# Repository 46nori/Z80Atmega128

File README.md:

# Z80ATmega128

[日本語版READMEはこちら](./README-ja.md)

## Overview

This project aims to build a Z80A system and run CP/M-80 natively on it.

You might be wondering why I chose the Z80 today. Well, it happened to be discovered in my collection of electronic components after being tucked away for 30 years. Moreover, it's an original Zilog Z80A from the NMOS process era, likely manufactured around 1980!  

However, rather than simply replicating a single-board microcontroller system from the 1980s, I've decided to take a different approach. Reproducing such a system lacks novelty and excitement, not to mention the difficulty of sourcing the necessary parts.

Hence, I've devised the following design principles:

1. A hybrid configuration utilizing both [Z80A](https://www.zilog.com/docs/z80/um0080.pdf) and [ATmega128-16AU](https://www.microchip.com/en-us/product/ATmega128) (AVR) microcontrollers.
2. I won't be using ROM; instead, a 64KB SRAM will be shared between the Z80A and AVR. AVR will manage the placement of the Z80's bootstrap code.
3. AVR firmware will handle the Z80 hardware I/O and interrupt cycles completely. **Any Z80's I/O devices can, in principle, be described by software!**
4. Design circuits using components that are as easy to procure as possible. (As of 2023, mainly in the Japanese electronic parts market.)

## Achievements

* CP/M 2.2 works directly on the Z80 processor.
* The system can boot CP/M from a microSD card containing the CP/M image file.
* CP/M 3 (Non-banked memory version) works as well.
* You can enjoy playing the text adventure game ZORK I, II and III !
* The printed circuit board (PCB) is available.
* Demo Video  

## Contents

```text
.
├── avr                      AVR firmware
├── z80                      Z80 software
│   ├── cpm22                CP/M-80 Ver2.2
│   │   ├── bios               BIOS
│   │   ├── sys                CPM.SYS(CCP/BDOS) and cpm.ihx(IPL+CCP/BDOS+BIOS)
│   │   └── image              CP/M 2.2 Disk image
│   └── cpm3                 CP/M 3 (CP/M Plus)
│       └── image              CP/M 3 Disk image
├── doc
│   ├── Hardware/            Hardware documents
│   ├── Software/            Software documents
│   └── README.md            Table of contents
└── schematics
    └── KiCad
        ├── *.kicad_sch      Schematic diagram
        └── *.kicad_pcb      PCB diagram
```

* [Document](doc/README.md)
  * [Z80ATmega128 Board Setup Guide](doc/SetupGuide_en.md)
  * [Hardware design document](doc/Hardware/Design.md)
* [Development log](doc/Diary.md)

## Required tools

* [Microchip Studio](https://www.microchip.com/en-us/tools-resources/develop/microchip-studio) for AVR v7.0 or later is required to build avr/.
* [AVRISP mkII](https://www.microchip.com/en-us/development-tool/ATAVRISP2) is required to program software(avr/) into ATmega128.
* Schematics and PCB are designed by [KiCad](https://www.kicad.org/) v7.0.
* [ASxxxx Cross Assemblers](https://shop-pdp.net/ashtml/asxxxx.php) to build the CP/M BIOS in z80/.
* [cpmtools](https://github.com/lipro-cpm4l/cpmtools) for creating CP/M disk images.

## Prototype

## PCB

## Schematic diagram

## License

GPLv3

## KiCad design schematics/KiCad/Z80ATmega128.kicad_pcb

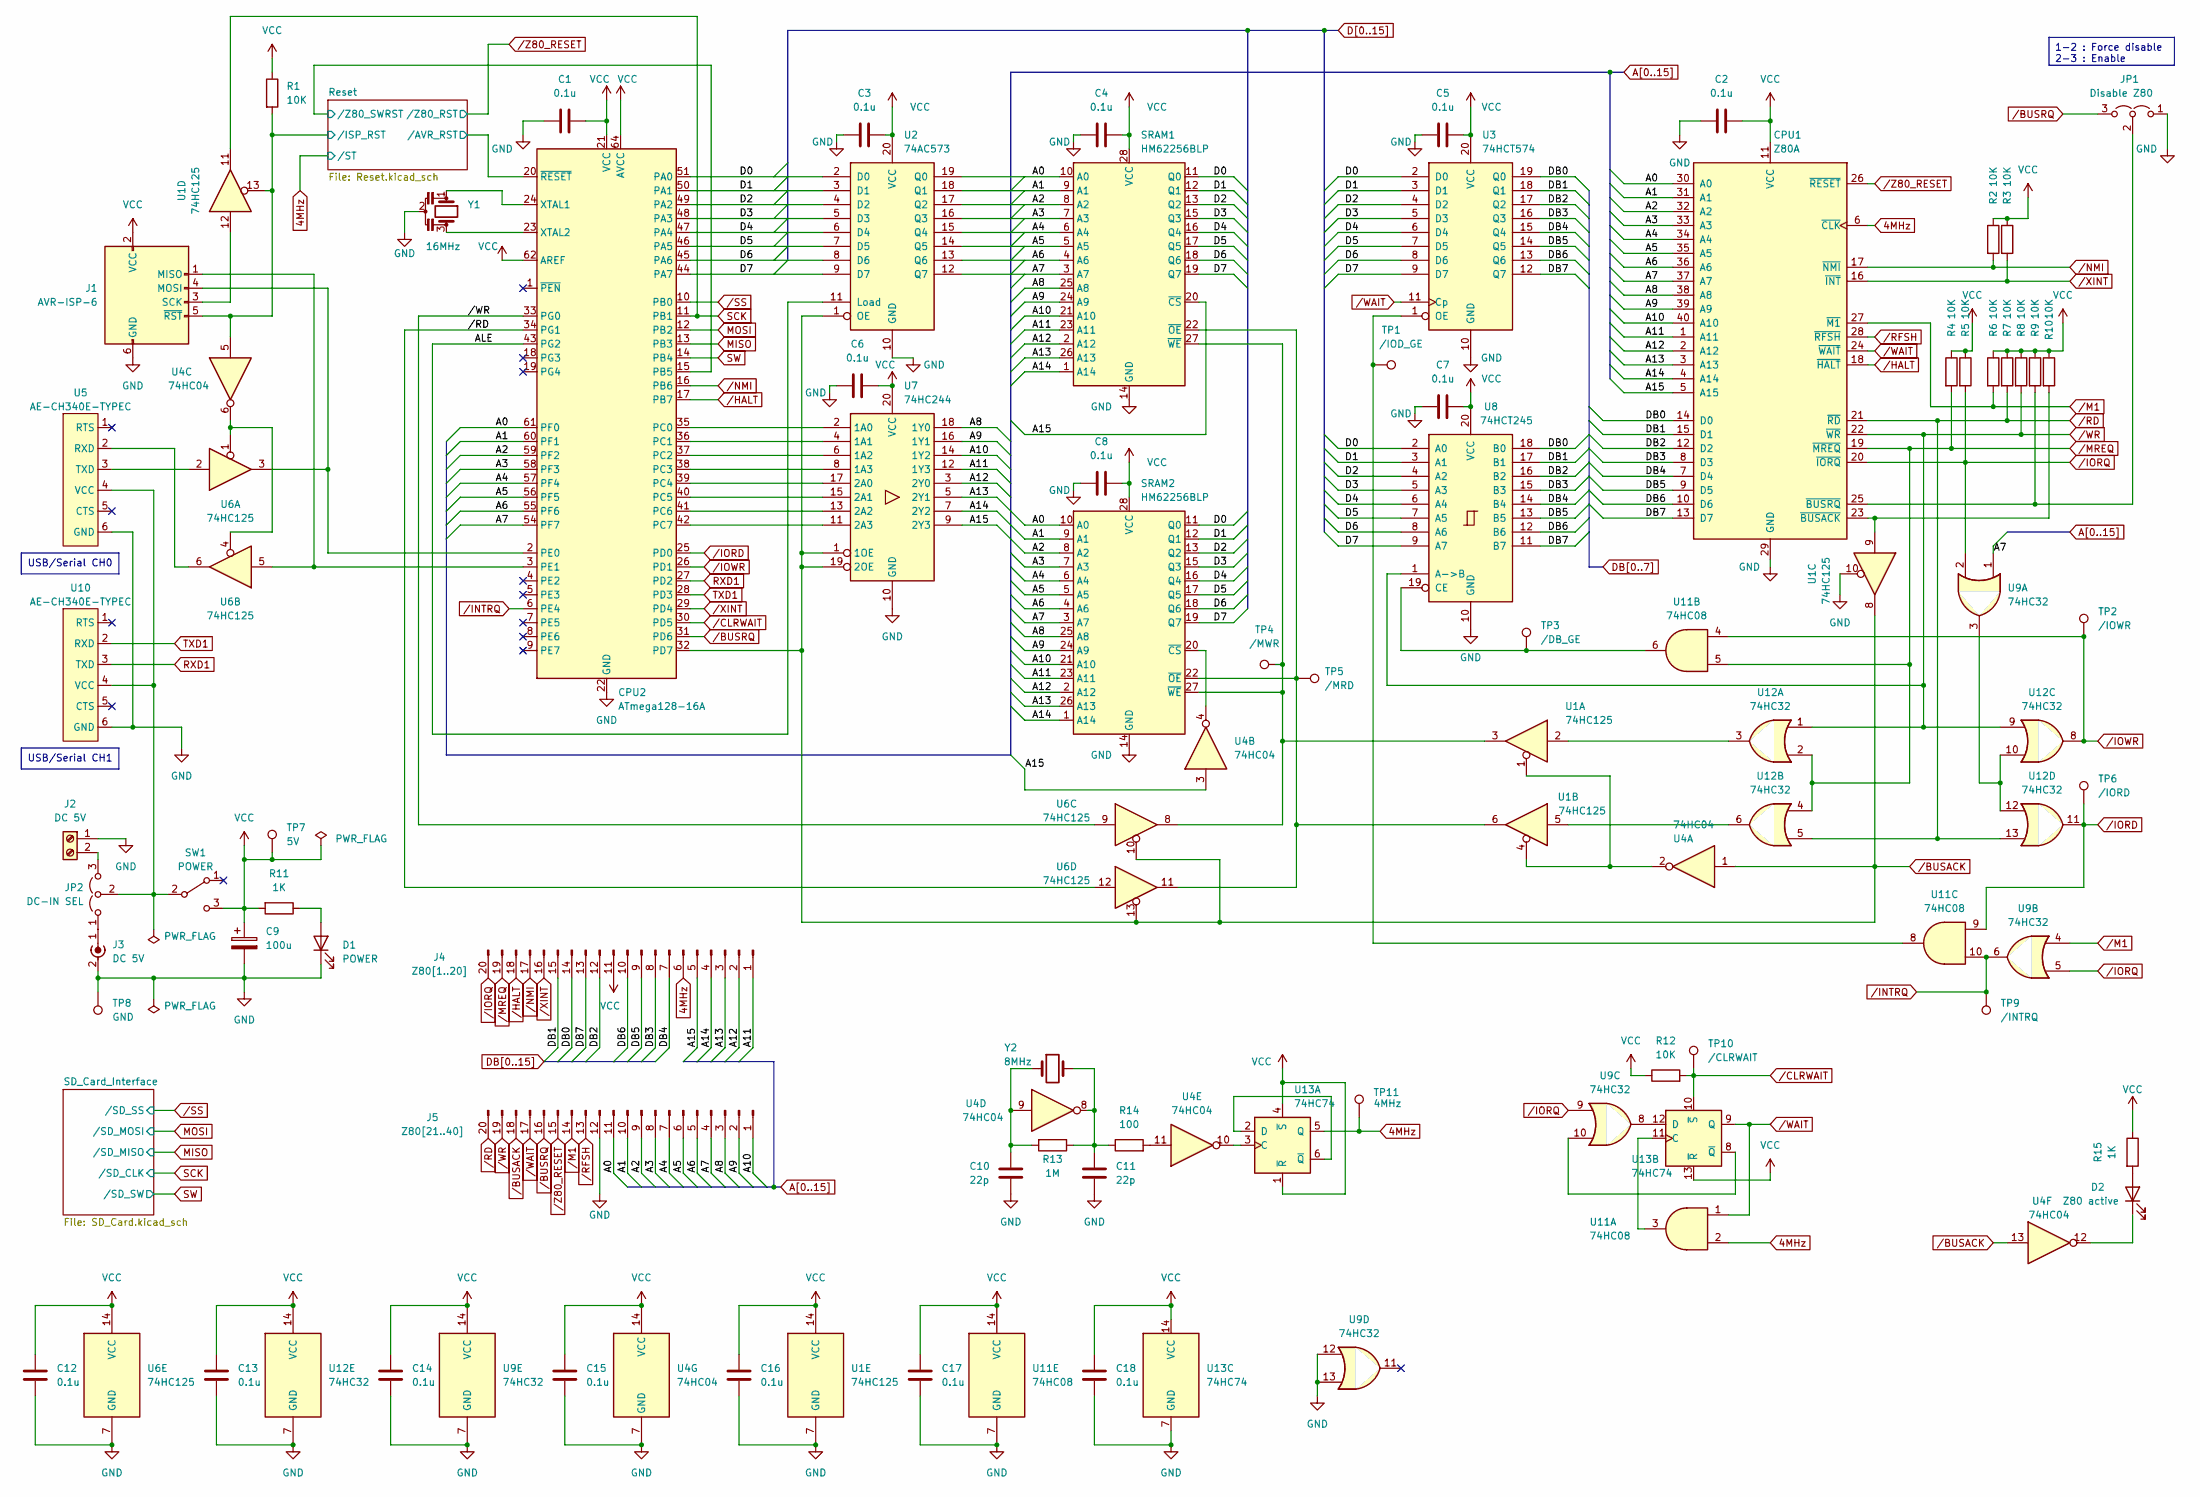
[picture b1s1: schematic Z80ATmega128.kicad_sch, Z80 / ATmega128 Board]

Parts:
C1, C2, C3, C4, C5, C6, C7, C8, C12, C13, C14, C15, C16, C17, C18: 0.1u; C_Disc_D3.8mm_W2.6mm_P2.50mm
C9: 100u; CP_Radial_Tantal_D5.0mm_P2.50mm
C10, C11: 22p; C_Disc_D3.8mm_W2.6mm_P2.50mm
CPU1: Z80A; DIP-40_W15.24mm_Socket
CPU2: ATmega128-16A; TQFP-64_14x14mm_P0.8mm
D1: POWER; LED_D3.0mm
D2: Z80 active; LED_D3.0mm
J1: AVR-ISP-6; PinHeader_2x03_P2.54mm_Vertical
J2: DC 5V; TerminalBlock_Altech_AK300-2_P5.00mm
J3: DC 5V; BarrelJack_Horizontal
J4: Z80[1..20]; PinHeader_1x20_P2.54mm_Vertical
J5: Z80[21..40]; PinHeader_1x20_P2.54mm_Vertical
JP1: Disable Z80; PinHeader_1x03_P2.54mm_Vertical
JP2: DC-IN SEL; PinHeader_1x03_P2.54mm_Vertical
R1, R2, R3, R4, R5, R6, R7, R8, R9, R10, R12: 10K; R_Axial_DIN0204_L3.6mm_D1.6mm_P7.62mm_Horizontal
R11, R15: 1K; R_Axial_DIN0204_L3.6mm_D1.6mm_P7.62mm_Horizontal
R13: 1M; R_Axial_DIN0204_L3.6mm_D1.6mm_P7.62mm_Horizontal
R14: 100; R_Axial_DIN0204_L3.6mm_D1.6mm_P7.62mm_Horizontal
SRAM1, SRAM2: HM62256BLP; DIP-28_W15.24mm_Socket
SW1: POWER; SW_Slide_1P2T_CK_OS102011MS2Q
TP1: /IOD_GE; TestPoint_Loop_D2.50mm_Drill1.0mm
TP2: /IOWR; TestPoint_Loop_D2.50mm_Drill1.0mm
TP3: /DB_GE; TestPoint_Loop_D2.50mm_Drill1.0mm
TP4: /MWR; TestPoint_Loop_D2.50mm_Drill1.0mm
TP5: /MRD; TestPoint_Loop_D2.50mm_Drill1.0mm
TP6: /IORD; TestPoint_Loop_D2.50mm_Drill1.0mm
TP7: 5V; TestPoint_Loop_D2.50mm_Drill1.0mm
TP8: GND; TestPoint_Loop_D2.50mm_Drill1.0mm
TP9: /INTRQ; TestPoint_Loop_D2.50mm_Drill1.0mm
TP10: /CLRWAIT; TestPoint_Loop_D2.50mm_Drill1.0mm
TP11: 4MHz; TestPoint_Loop_D2.50mm_Drill1.0mm
U1, U6: 74HC125; DIP-14_W7.62mm_Socket
U2: 74AC573; DIP-20_W7.62mm_Socket
U3: 74HCT574; DIP-20_W7.62mm_Socket
U4: 74HC04; DIP-14_W7.62mm_Socket
U5, U10: AE-CH340E-TYPEC; PinHeader_1x06_P2.54mm_Vertical
U7: 74HC244; DIP-20_W7.62mm_Socket
U8: 74HCT245; DIP-20_W7.62mm_Socket
U9, U12: 74HC32; DIP-14_W7.62mm_Socket
U11: 74HC08; DIP-14_W7.62mm_Socket
U13: 74HC74; DIP-14_W7.62mm_Socket
Y1: 16MHz; Resonator_Murata_CSTLSxxxX-3Pin_W5.5mm_H3.0mm
Y2: 8MHz; Crystal_HC18-U_Vertical

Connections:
4MHz: CPU1.6 (~CLK), J4.6, TP11.1, U11.2, U13.5 (Q); also elsewhere on the board
/ALE: CPU2.43 (PG2), U2.11 (Load)
/Reset//AVR_RST: CPU2.20 (~RESET); also elsewhere on the board
/Reset//ISP_RST: J1.5 (~RST), R1.2, U1.13, U4.5; also elsewhere on the board
/Reset//Z80_SWRST: CPU2.15 (PB5); also elsewhere on the board
A0: CPU1.30 (A0), CPU2.61 (PF0), J5.11, SRAM1.10 (A0), SRAM2.10 (A0), U2.19 (Q0)
A1: CPU1.31 (A1), CPU2.60 (PF1), J5.10, SRAM1.9 (A1), SRAM2.9 (A1), U2.18 (Q1)
A2: CPU1.32 (A2), CPU2.59 (PF2), J5.9, SRAM1.8 (A2), SRAM2.8 (A2), U2.17 (Q2)
A3: CPU1.33 (A3), CPU2.58 (PF3), J5.8, SRAM1.7 (A3), SRAM2.7 (A3), U2.16 (Q3)
A4: CPU1.34 (A4), CPU2.57 (PF4), J5.7, SRAM1.6 (A4), SRAM2.6 (A4), U2.15 (Q4)
A5: CPU1.35 (A5), CPU2.56 (PF5), J5.6, SRAM1.5 (A5), SRAM2.5 (A5), U2.14 (Q5)
A6: CPU1.36 (A6), CPU2.55 (PF6), J5.5, SRAM1.4 (A6), SRAM2.4 (A6), U2.13 (Q6)
A7: CPU1.37 (A7), CPU2.54 (PF7), J5.4, SRAM1.3 (A7), SRAM2.3 (A7), U2.12 (Q7), U9.1
A8: CPU1.38 (A8), J5.3, SRAM1.25 (A8), SRAM2.25 (A8), U7.18 (1Y0)
A9: CPU1.39 (A9), J5.2, SRAM1.24 (A9), SRAM2.24 (A9), U7.16 (1Y1)
A10: CPU1.40 (A10), J5.1, SRAM1.21 (A10), SRAM2.21 (A10), U7.14 (1Y2)
A11: CPU1.1 (A11), J4.1, SRAM1.23 (A11), SRAM2.23 (A11), U7.12 (1Y3)
A12: CPU1.2 (A12), J4.2, SRAM1.2 (A12), SRAM2.2 (A12), U7.3 (2Y0)
A13: CPU1.3 (A13), J4.3, SRAM1.26 (A13), SRAM2.26 (A13), U7.5 (2Y1)
A14: CPU1.4 (A14), J4.4, SRAM1.1 (A14), SRAM2.1 (A14), U7.7 (2Y2)
A15: CPU1.5 (A15), J4.5, SRAM1.20 (~CS), U4.3, U7.9 (2Y3)
D0: CPU2.51 (PA0), SRAM1.11 (Q0), SRAM2.11 (Q0), U2.2 (D0), U3.2 (D0), U8.2 (A0)
D1: CPU2.50 (PA1), SRAM1.12 (Q1), SRAM2.12 (Q1), U2.3 (D1), U3.3 (D1), U8.3 (A1)
D2: CPU2.49 (PA2), SRAM1.13 (Q2), SRAM2.13 (Q2), U2.4 (D2), U3.4 (D2), U8.4 (A2)
D3: CPU2.48 (PA3), SRAM1.15 (Q3), SRAM2.15 (Q3), U2.5 (D3), U3.5 (D3), U8.5 (A3)
D4: CPU2.47 (PA4), SRAM1.16 (Q4), SRAM2.16 (Q4), U2.6 (D4), U3.6 (D4), U8.6 (A4)
D5: CPU2.46 (PA5), SRAM1.17 (Q5), SRAM2.17 (Q5), U2.7 (D5), U3.7 (D5), U8.7 (A5)
D6: CPU2.45 (PA6), SRAM1.18 (Q6), SRAM2.18 (Q6), U2.8 (D6), U3.8 (D6), U8.8 (A6)
D7: CPU2.44 (PA7), SRAM1.19 (Q7), SRAM2.19 (Q7), U2.9 (D7), U3.9 (D7), U8.9 (A7)
DB0: CPU1.14 (D0), J4.14, U3.19 (Q0), U8.18 (B0)
DB1: CPU1.15 (D1), J4.15, U3.18 (Q1), U8.17 (B1)
DB2: CPU1.12 (D2), J4.12, U3.17 (Q2), U8.16 (B2)
DB3: CPU1.8 (D3), J4.8, U3.16 (Q3), U8.15 (B3)
DB4: CPU1.7 (D4), J4.7, U3.15 (Q4), U8.14 (B4)
DB5: CPU1.9 (D5), J4.9, U3.14 (Q5), U8.13 (B5)
DB6: CPU1.10 (D6), J4.10, U3.13 (Q6), U8.12 (B6)
DB7: CPU1.13 (D7), J4.13, U3.12 (Q7), U8.11 (B7)
MISO: CPU2.13 (PB3); also elsewhere on the board
MOSI: CPU2.12 (PB2); also elsewhere on the board
unnamed: C10.1, R13.2, U4.9, Y2.1
unnamed: C11.1, R13.1, R14.1, U4.8, Y2.2
unnamed: CPU1.23 (~BUSACK), R10.2, U1.9
unnamed: CPU1.25 (~BUSRQ), JP1.2 (C), R9.2
unnamed: CPU2.35 (PC0), U7.2 (1A0)
unnamed: CPU2.36 (PC1), U7.4 (1A1)
unnamed: CPU2.37 (PC2), U7.6 (1A2)
unnamed: CPU2.38 (PC3), U7.8 (1A3)
unnamed: CPU2.39 (PC4), U7.17 (2A0)
unnamed: CPU2.40 (PC5), U7.15 (2A1)
unnamed: CPU2.41 (PC6), U7.13 (2A2)
unnamed: CPU2.42 (PC7), U7.11 (2A3)
unnamed: CPU2.2 (PE0), J1.4 (MOSI), U6.3
unnamed: CPU2.3 (PE1), J1.1 (MISO), U6.5
unnamed: CPU2.24 (XTAL1), Y1.1
unnamed: CPU2.23 (XTAL2), Y1.3
unnamed: D1.2 (A), R11.1
unnamed: D2.2 (A), R15.2
unnamed: D2.1 (K), U4.12
unnamed: J1.3 (SCK), U1.12
unnamed: R14.2, U4.11
unnamed: SRAM1.22 (~OE), SRAM2.22 (~OE), TP5.1, U1.6, U6.11
unnamed: SRAM1.27 (~WE), SRAM2.27 (~WE), TP4.1, U1.3, U6.8
unnamed: SRAM2.20 (~CS), U4.4
unnamed: U1.1, U1.4, U4.2
unnamed: U1.2, U12.3
unnamed: U1.5, U12.6
unnamed: TP1.1, U3.1 (OE), U11.8
unnamed: U4.6, U6.1, U6.4
unnamed: U5.2 (RXD), U6.6
unnamed: U5.3 (TXD), U6.2
unnamed: TP3.1, U8.19 (CE), U11.6
unnamed: U9.3, U12.10, U12.12
unnamed: U4.10, U13.3 (C)
unnamed: U13.2 (D), U13.6 (~Q)
unnamed: U11.3, U13.11 (C)
unnamed: U9.8, U13.12 (D)
unnamed: U9.10, U13.8 (~Q)
RXD1: CPU2.27 (PD2), U10.3 (TXD)
SCK: CPU2.11 (PB1), U1.11; also elsewhere on the board
SW: CPU2.14 (PB4); also elsewhere on the board
TXD1: CPU2.28 (PD3), U10.2 (RXD)
/BUSACK: CPU2.32 (PD7), J5.18, U1.8, U2.1 (OE), U4.1, U4.13, U6.10, U6.13, U7.1 (1OE), U7.19 (2OE)
/BUSRQ: CPU2.31 (PD6), J5.16, JP1.3 (B)
/CLRWAIT: CPU2.30 (PD5), R12.2, TP10.1, U13.10 (~S)
/HALT: CPU1.18 (~HALT), CPU2.17 (PB7), J4.18
/INTRQ: CPU2.6 (PE4), TP9.1, U9.6, U11.10
/IORD: CPU2.25 (PD0), TP6.1, U11.9, U12.11
/IORQ: CPU1.20 (~IORQ), J4.20, R5.2, U9.2, U9.5, U9.9
/IOWR: CPU2.26 (PD1), TP2.1, U11.4, U12.8
/M1: CPU1.27 (~M1), J5.14, R6.2, U9.4
/MREQ: CPU1.19 (~MREQ), J4.19, R4.2, U11.5, U12.2, U12.4
/NMI: CPU1.17 (~NMI), CPU2.16 (PB6), J4.17, R2.2
/RD: CPU1.21 (~RD), CPU2.34 (PG1), J5.20, R7.2, U6.12, U12.5, U12.13
/RFSH: CPU1.28 (~RFSH), J5.13
/SS: CPU2.10 (PB0); also elsewhere on the board
/WAIT: CPU1.24 (~WAIT), J5.17, U3.11 (Cp), U11.1, U13.9 (Q)
/WR: CPU1.22 (~WR), CPU2.33 (PG0), J5.19, R8.2, U6.9, U8.1 (A->B), U12.1, U12.9
/XINT: CPU1.16 (~INT), CPU2.29 (PD4), J4.16, R3.2
/Z80_RESET: CPU1.26 (~RESET), J5.15; also elsewhere on the board

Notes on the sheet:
1-2 : Force disable 2-3 : Enable
USB/Serial CH0
USB/Serial CH1

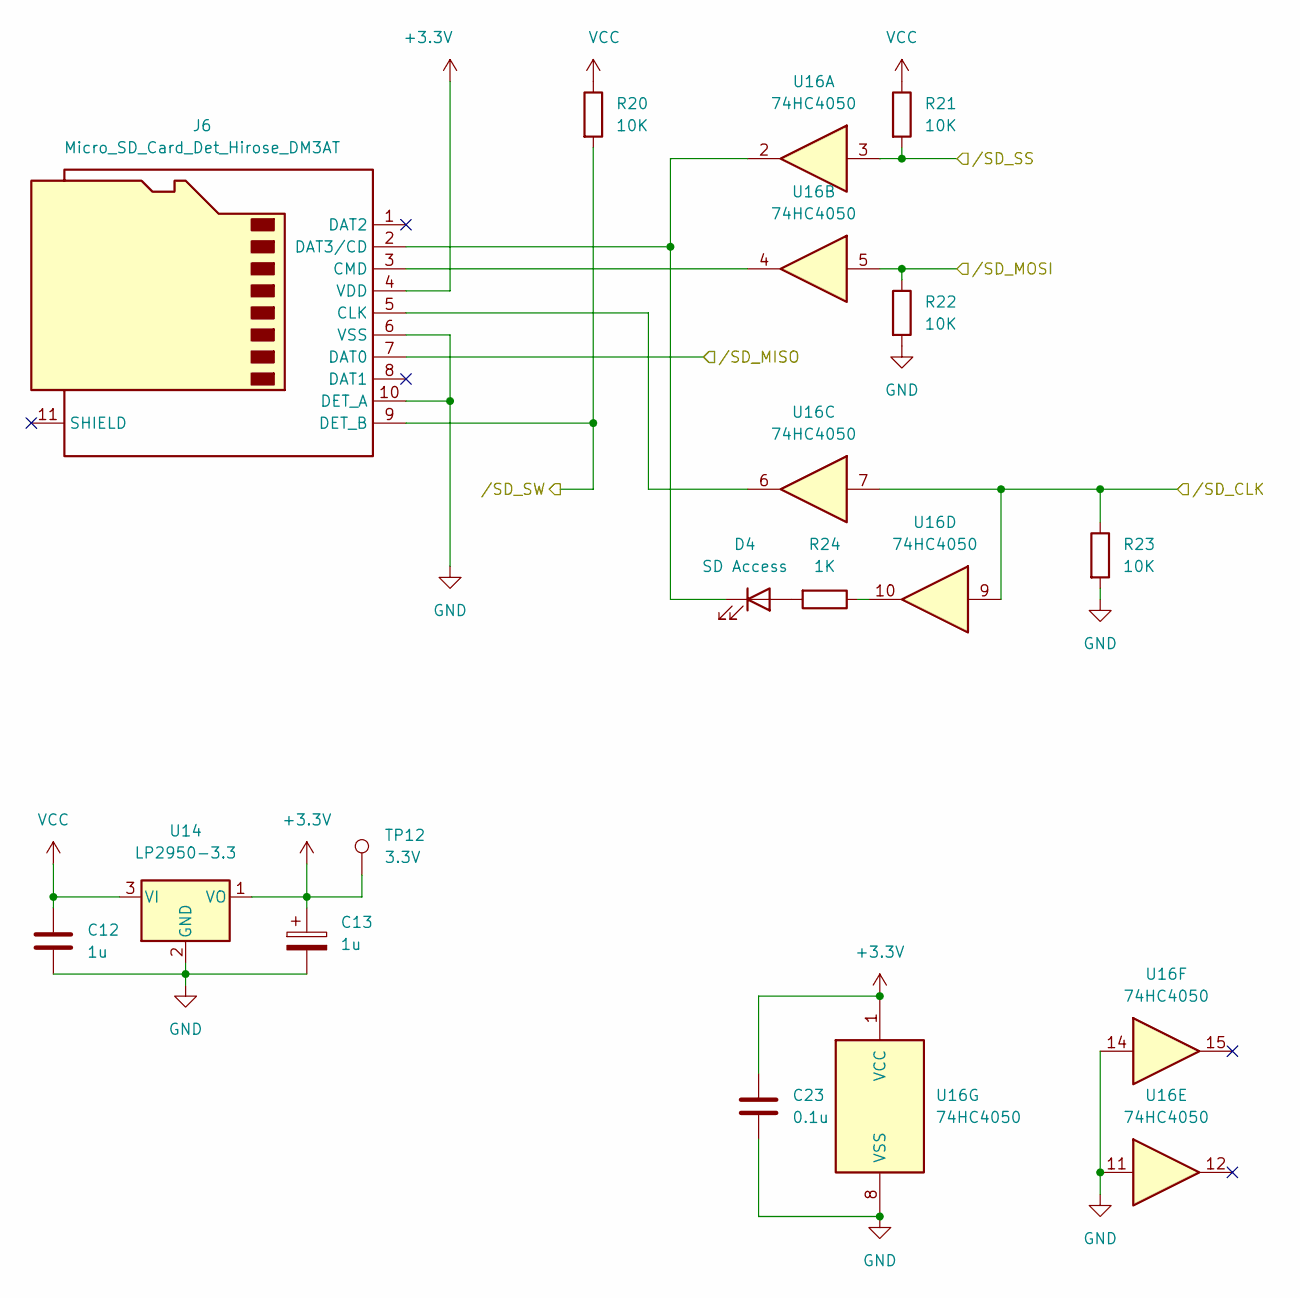
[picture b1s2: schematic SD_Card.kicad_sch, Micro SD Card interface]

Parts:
C12, C13: 1u; CP_Radial_Tantal_D5.0mm_P2.50mm
C23: 0.1u; C_Disc_D3.8mm_W2.6mm_P2.50mm
D4: SD Access; LED_D3.0mm
J6: Micro_SD_Card_Det_Hirose_DM3AT; microSD_HC_Hirose_DM3AT-SF-PEJM5
R20, R21, R22, R23: 10K; R_Axial_DIN0204_L3.6mm_D1.6mm_P7.62mm_Horizontal
R24: 1K; R_Axial_DIN0204_L3.6mm_D1.6mm_P7.62mm_Horizontal
TP12: 3.3V; TestPoint_Loop_D2.50mm_Drill1.0mm
U14: LP2950-3.3; TO-92_Inline
U16: 74HC4050; DIP-16_W7.62mm_Socket

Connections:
MISO: J6.7 (DAT0); also elsewhere on the board
MOSI: R22.1, U16.5; also elsewhere on the board
unnamed: D4.2 (A), R24.2
unnamed: D4.1 (K), J6.2 (DAT3/CD), U16.2
unnamed: J6.5 (CLK), U16.6
unnamed: J6.3 (CMD), U16.4
unnamed: R24.1, U16.10
SCK: R23.1, U16.7, U16.9; also elsewhere on the board
SW: J6.9 (DET_B), R20.2; also elsewhere on the board
/SS: R21.2, U16.3; also elsewhere on the board

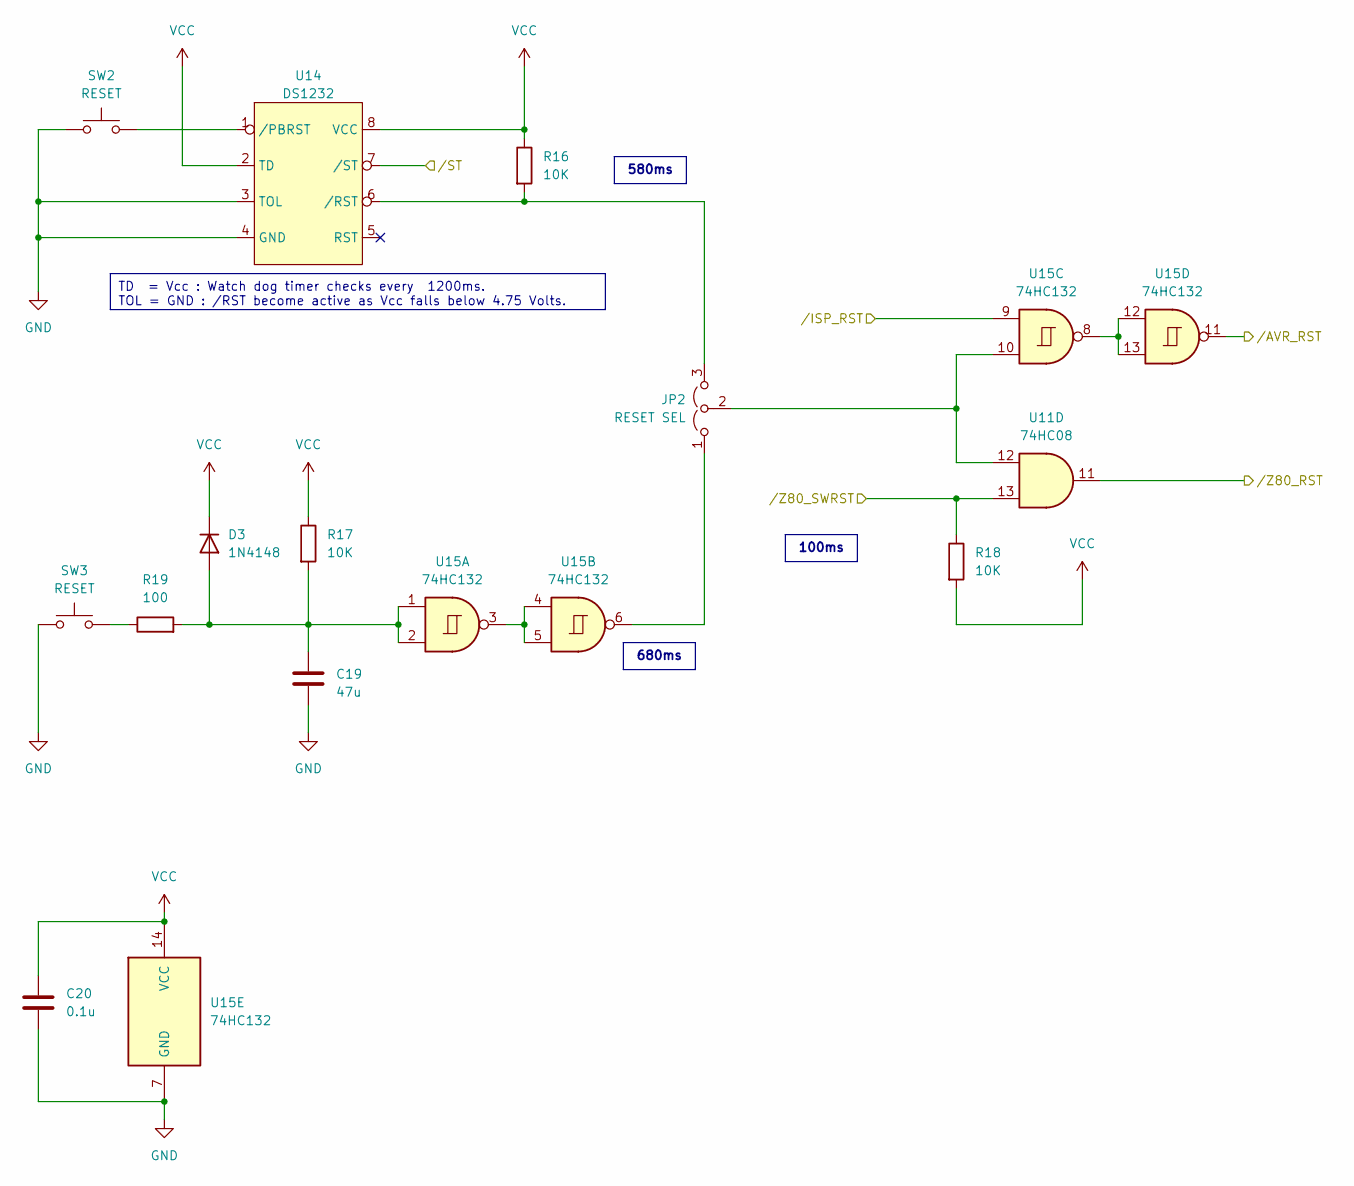
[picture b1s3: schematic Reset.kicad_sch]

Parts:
C19: 47u; CP_Radial_Tantal_D5.0mm_P2.50mm
C20: 0.1u; C_Disc_D3.8mm_W2.6mm_P2.50mm
D3: 1N4148; D_DO-35_SOD27_P7.62mm_Horizontal
JP2: RESET SEL; PinHeader_1x03_P2.54mm_Vertical
R16, R17, R18: 10K; R_Axial_DIN0204_L3.6mm_D1.6mm_P7.62mm_Horizontal
R19: 100; R_Axial_DIN0204_L3.6mm_D1.6mm_P7.62mm_Horizontal
SW2, SW3: RESET; SW_PUSH_6mm_H7.3mm
U11: 74HC08; DIP-14_W7.62mm_Socket
U14: DS1232; DIP-8_W7.62mm
U15: 74HC132; DIP-14_W7.62mm_Socket

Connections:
4MHz: U14.7 (/ST); also elsewhere on the board
/Reset//AVR_RST: U15.11; also elsewhere on the board
/Reset//ISP_RST: U15.9; also elsewhere on the board
/Reset//Z80_SWRST: R18.1, U11.13; also elsewhere on the board
unnamed: C19.1, D3.2 (A), R17.2, R19.2, U15.1, U15.2
unnamed: R19.1, SW3.2
unnamed: U15.3, U15.4, U15.5
unnamed: U15.8, U15.12, U15.13
/Z80_RESET: U11.11; also elsewhere on the board

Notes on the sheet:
680ms
580ms
TD = Vcc : Watch dog timer checks every 1200ms. TOL = GND : /RST become active as Vcc falls below 4.75 Volts.
100ms

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
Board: 2 copper layers, 98 parts (0 on the bottom side), 118 nets, no tracks yet.

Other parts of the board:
C21, C22: 1u; CP_Radial_Tantal_D5.0mm_P2.50mm
JP3: RESET SEL; PinHeader_1x03_P2.54mm_Vertical
U17: LP2950-3.3; TO-92_Inline

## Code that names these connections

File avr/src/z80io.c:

/*
 * z80io.c
 *
 * Created: 2023/04/07 21:44:00
 *  Author: 46nori
 */ 
#include "z80io.h"
#include "xconsoleio.h"

//
// Initialize external memory settings
//
void ExtMem_Init(int wait)
{
	// WAIT setting for external SRAM
	if (wait < 2) {
		// SRAM access time < 100ns
		SET_BIT(MCUCR, SRW10);					// 1wait(SRW10=1)
		SET_BYTE(XMCRA, _BV(SRW00));			// 1wait(SRW0x=01, SRW11=0)
	} else {
		// SRAM access time >= 100ns
		CLR_BIT(MCUCR, SRW10);					// 2wait(SRW10=0)
		SET_BYTE(XMCRA, _BV(SRW01)|_BV(SRW11));	// 2wait(SRW0x=10, SRW11=1)
	}
	SET_BYTE(XMCRB, 0x00);		// Disable external memory bus-keeper
	
	SET_BYTE(PORTA, 0xff);		// Set PORTA as Hi-Z
	SET_BYTE(DDRA,  0x00);		//
	SET_BYTE(PORTC, 0x00);		// Force higher address disable
	SET_BYTE(DDRC,  0xff);		// Set PORTC as output
}

//
// Attach external memory and make Z80 suspend
// Caution: Do NOT call at the interrupt handler
//          for Z80 (/IN0, /INT1, /INT4)
//
void ExtMem_attach(void)
{
	Z80_BUSREQ(1);				// Acquire memory bus
	SET_BIT(MCUCR, SRE);		// Enable XMEM
}

//
// Detach external memory and let Z80 be active
//
void ExtMem_detach(void)
{
	CLR_BIT(MCUCR, SRE);		// Disable XMEM
	Z80_BUSREQ(0);				// Release memory bus
}

//
// Set shadow area to access hiding area of external memory
//
void *ExtMem_map(void)
{
	SET_BYTE(XMCRB, 0x03);	// Enable shadow
	return (void *)0x2000;
}

void ExtMem_unmap(void)
{
	SET_BYTE(XMCRB, 0x00);	// Disable shadow
}

//
// Z80 control
//
//
// Invoke /BUSRQ (PD6)
//
void Z80_BUSREQ(int st)
{
	if (st) {
		// Enable /BUSREQ
		CLR_BIT(PORTD, PORTD6);
		// Wait for /BUSACK
		while (PIND & _BV(PORTD7)) {
			//x_putchar('#');		// debug
		}
	} else {
		// Disable /BUSREQ
		SET_BIT(PORTD, PORTD6);
	}
}

//
// Invoke /RESET (PB5) to reset Z80
//
void Z80_RESET(void)
{
	ExtMem_detach();
	// Send reset pulse
	CLR_BIT(PORTB, PORTB5);
	_delay_ms(10);
	SET_BIT(PORTB, PORTB5);
}

//
// Invoke /NMI (PB6) for Z80 NMI
//   /NMI required >80ns low period in Z80A
void Z80_NMI(void)
{
	CLR_BIT(PORTB, PORTB6);		// t_w(/NML) > 80ns
	asm("NOP");					// 62.5ns (=1CLK@16MHz)
	asm("NOP");					// 62.5ns (=1CLK@16MHz)
	SET_BIT(PORTB, PORTB6);	
}

//
// Reset Z80 and go to specified address 
//   adr is jump address
//   0x0000-0x0003 is overwritten with 'JP adr'.
//
void Z80_RESET_GO(uint8_t *adr)
{
	SET_BIT(MCUCR, SRE);		// Enable XMEM
	uint8_t *p = (uint8_t *)ExtMem_map();	// 0x0000
	p[0] = 0xc3;							// JP
	p[1] = (uint16_t)adr & 0xff;			// Low address
	p[2] = ((uint16_t)adr >> 8) & 0xff;		// High address
	ExtMem_unmap();
	CLR_BIT(MCUCR, SRE);		// Disable XMEM
	Z80_RESET();
}

//
// Invoke /XINT (PD4) for Z80 INT
//
// vector should be set as following:
//   Mode2 : interrupt number * 2
//           e.g., 16 should be set in case of INT8
//   Mode0 : Z80 instruction
//

volatile uint8_t z80_int_vector;

//
// Interrupt vector FIFO queue
//
#define INT_QUEUE_SIZE 8
static volatile uint8_t int_queue[INT_QUEUE_SIZE];
static volatile uint8_t int_queue_head = 0;
static volatile uint8_t int_queue_tail = 0;

void Z80_EXTINT_low(uint8_t vector)
{
	z80_int_vector = vector;
	CLR_BIT(PORTD, PORTD4);		// /INT = Low
}

void Z80_EXTINT_High(void)
{
	SET_BIT(PORTD, PORTD4);		// /INT = High
}

void Z80_EXTINT_enqueue(uint8_t vector)
{
	uint8_t sreg = SREG;
	cli();
	uint8_t next = (int_queue_tail + 1) % INT_QUEUE_SIZE;
	if (next != int_queue_head) {
		int_queue[int_queue_tail] = vector;
		int_queue_tail = next;
	}
	// Assert /INT only when queue transitions from empty (count == 1)
	uint8_t count = (int_queue_tail - int_queue_head + INT_QUEUE_SIZE) % INT_QUEUE_SIZE;
	if (count == 1) {
		z80_int_vector = vector;
		CLR_BIT(PORTD, PORTD4);		// /INT = Low
	}
	SREG = sreg;
}

uint8_t Z80_EXTINT_dequeue(void)
{
	if (int_queue_head == int_queue_tail) {
		return 0;	// queue empty
	}
	int_queue_head = (int_queue_head + 1) % INT_QUEUE_SIZE;
	if (int_queue_head != int_queue_tail) {
		z80_int_vector = int_queue[int_queue_head];
		return 1;	// more entries remain
	}
	return 0;	// queue now empty
}

void Z80_EXTINT(uint8_t vector)
{
	Z80_EXTINT_low(vector);		// /INT = Low
	_delay_us(1);				// t_s(IT) > 80ns
	Z80_EXTINT_High();			// /INT = High
}

//
// Clear /CLRWAIT (PD5) to deactivate Z80 /WAIT
// Pulse width must be >250ns (Z80 1CLK@4MHz)
//   62.5ns(AVR 1CLK@16MHz) * 5CLK = 312.5ns
void Z80_CLRWAIT(void)
{
	CLR_BIT(PORTD, PORTD5);
	asm("NOP");					// 1 CLK
	asm("NOP");					// 1 CLK
	asm("NOP");					// 1 CLK
	SET_BIT(PORTD, PORTD5);		// 2 CLK
}

//
// Set HALT instruction at 0x0000 to stay Z80 halt after reset
//
void Z80_HALT(void)
{
	SET_BIT(MCUCR, SRE);		// Enable XMEM
	*(volatile uint8_t *)ExtMem_map() = 0x76;	// HALT instruction
	ExtMem_unmap();
	CLR_BIT(MCUCR, SRE);		// Disable XMEM
}

//
// Sense Z80 /BUSRQ
//   return 0(Low), 1(High)
//
int Is_Z80_BUSRQ(void)
{
	return PIND & _BV(PORTD6) ? 1 : 0;
}

//
// Sense Z80 /BUSACK
//   return 0(Low), 1(High)
//
int Is_Z80_BUSACK(void)
{
	return PIND & _BV(PORTD7) ? 1 : 0;
}

//
// Sense Z80 /HALT
//   return 0(Low), 1(High)
//
int Is_Z80_HALT(void)
{
	return PINB & _BV(PORTB7) ? 1 : 0;
}

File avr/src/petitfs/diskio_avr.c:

/*-------------------------------------------------------------------------*/
/* PFF - Low level disk control module for AVR							   */
/* Modified from (C)ChaN, 2014											   */
/*-------------------------------------------------------------------------*/
#define F_CPU 16000000UL		// Workaround

#include "pff.h"
#include "diskio.h"

/*-------------------------------------------------------------------------*/
/* Platform dependent macros and functions MODIFY FOR YOUR DEVICE           */
/*-------------------------------------------------------------------------*/

#include <avr/io.h> /* Device specific include files */

#define SPIPORT  PORTB
#define SPI_CS   _BV(PORTB0) //(1 << 0)  /* PB0 */
#define SPI_SCK  _BV(PORTB1) //(1 << 1)  /* PB1 */
#define SPI_MOSI _BV(PORTB2) //(1 << 2)  /* PB2 SD card DI */
#define SPI_MISO _BV(PORTB3) //(1 << 3)  /* PB3 SD card DO */

/* Port controls  (Platform dependent) */
#define SELECT()   SPIPORT &= ~SPI_CS /* CS = L */
#define DESELECT() SPIPORT |= SPI_CS  /* CS = H */
#define SELECTING ((DDRB & SPI_CS) && !(PORTB & SPI_CS))

static void init_spi(void)
{
	/* SPI pins */
	DDRB  |= (SPI_MOSI | SPI_CS | SPI_SCK); /* Set outputs */
	PORTB |= SPI_MISO; /* Enable pull-up on SPI_MISO (SD card DO) */

	SPCR = _BV(SPE)  |	// Enable SPI
	       _BV(MSTR) |	// Master mode
		   _BV(SPR1);	// SPI prescaler to give 100-400kHz clock
						// 1/64 With 16MHz F_CPU
}

static uint8_t spi(uint8_t d)
{
	SPDR = d;
	while (!(SPSR & _BV(SPIF)))
	;
	return SPDR;
}

static void xmit_spi(uint8_t d)
{
	spi(d);
}

static uint8_t rcv_spi(void)
{
	return spi(0xFF);
}

/*--------------------------------------------------------------------------

   Module Private Functions

---------------------------------------------------------------------------*/

/* Definitions for MMC/SDC command */
#define CMD0 (0x40 + 0)    /* GO_IDLE_STATE */
#define CMD1 (0x40 + 1)    /* SEND_OP_COND (MMC) */
#define ACMD41 (0xC0 + 41) /* SEND_OP_COND (SDC) */
#define CMD8 (0x40 + 8)    /* SEND_IF_COND */
#define CMD16 (0x40 + 16)  /* SET_BLOCKLEN */
#define CMD17 (0x40 + 17)  /* READ_SINGLE_BLOCK */
#define CMD24 (0x40 + 24)  /* WRITE_BLOCK */
#define CMD55 (0x40 + 55)  /* APP_CMD */
#define CMD58 (0x40 + 58)  /* READ_OCR */

/* Card type flags (CardType) */
#define CT_MMC 0x01   /* MMC ver 3 */
#define CT_SD1 0x02   /* SD ver 1 */
#define CT_SD2 0x04   /* SD ver 2 */
#define CT_BLOCK 0x08 /* Block addressing */

BYTE CardType = 0;

/*-----------------------------------------------------------------------*/
/* Send a command packet to MMC                                          */
/*-----------------------------------------------------------------------*/
static BYTE send_cmd(BYTE  cmd, /* 1st byte (Start + Index) */
                     DWORD arg  /* Argument (32 bits) */
)
{
	BYTE n, res;

	if (cmd & 0x80) { /* ACMD<n> is the command sequence of CMD55-CMD<n> */
		cmd &= 0x7F;
		res = send_cmd(CMD55, 0);
		if (res > 1)
			return res;
	}

	/* Select the card */
	DESELECT();
	rcv_spi();
	SELECT();
	rcv_spi();

	/* Send a command packet */
	xmit_spi(cmd);               /* Start + Command index */
	xmit_spi((BYTE)(arg >> 24)); /* Argument[31..24] */
	xmit_spi((BYTE)(arg >> 16)); /* Argument[23..16] */
	xmit_spi((BYTE)(arg >> 8));  /* Argument[15..8] */
	xmit_spi((BYTE)arg);         /* Argument[7..0] */
	n = 0x01;                    /* Dummy CRC + Stop */
	if (cmd == CMD0)
		n = 0x95; /* Valid CRC for CMD0(0) */
	if (cmd == CMD8)
		n = 0x87; /* Valid CRC for CMD8(0x1AA) */
	xmit_spi(n);

	/* Receive a command response */
	n = 10; /* Wait for a valid response in timeout of 10 attempts */
	do {
		res = rcv_spi();
	} while ((res & 0x80) && --n);

	return res; /* Return with the response value */
}

/*--------------------------------------------------------------------------

   Public Functions

---------------------------------------------------------------------------*/

/*-----------------------------------------------------------------------*/
/* Initialize Disk Drive                                                 */
/*-----------------------------------------------------------------------*/

DSTATUS disk_initialize(void)
{
	BYTE n, cmd, ty, ocr[4];
	UINT tmr;

#if _USE_WRITE
	if (CardType && SELECTING)
		disk_writep(0, 0); /* Finalize write process if it is in progress */
#endif

	init_spi(); /* Initialize ports to control MMC */
	DESELECT();
	for (n = 10; n; n--)
		rcv_spi(); /* 80 dummy clocks with CS=H */

	ty = 0;
	if (send_cmd(CMD0, 0) == 1) {         /* GO_IDLE_STATE */
		if (send_cmd(CMD8, 0x1AA) == 1) { /* SDv2 */
			for (n = 0; n < 4; n++)
				ocr[n] = rcv_spi();                 /* Get trailing return value of R7 resp */
			if (ocr[2] == 0x01 && ocr[3] == 0xAA) { /* The card can work at vdd range of 2.7-3.6V */
				for (tmr = 10000; tmr && send_cmd(ACMD41, 1UL << 30); tmr--)
					_delay_us(100);                   /* Wait for leaving idle state (ACMD41 with HCS bit) */
				if (tmr && send_cmd(CMD58, 0) == 0) { /* Check CCS bit in the OCR */
					for (n = 0; n < 4; n++)
						ocr[n] = rcv_spi();
					ty = (ocr[0] & 0x40) ? CT_SD2 | CT_BLOCK : CT_SD2; /* SDv2 (HC or SC) */
				}
			}
		} else { /* SDv1 or MMCv3 */
			if (send_cmd(ACMD41, 0) <= 1) {
				ty  = CT_SD1;
				cmd = ACMD41; /* SDv1 */
			} else {
				ty  = CT_MMC;
				cmd = CMD1; /* MMCv3 */
			}
			for (tmr = 10000; tmr && send_cmd(cmd, 0); tmr--)
				_delay_us(100);                    /* Wait for leaving idle state */
			if (!tmr || send_cmd(CMD16, 512) != 0) /* Set R/W block length to 512 */
				ty = 0;
		}
	}
	CardType = ty;
	DESELECT();
	rcv_spi();

	return ty ? 0 : STA_NOINIT;
}

/*-----------------------------------------------------------------------*/
/* Read partial sector                                                   */
/*-----------------------------------------------------------------------*/

DRESULT disk_readp(BYTE *buff,   /* Pointer to the read buffer (NULL:Forward to the stream) */
                   DWORD sector, /* Sector number (LBA) */
                   UINT  offset, /* Byte offset to read from (0..511) */
                   UINT  count   /* Number of bytes to read (ofs + cnt mus be <= 512) */
)
{
	DRESULT res;
	BYTE    rc;
	UINT    bc;

	if (!(CardType & CT_BLOCK))
		sector *= 512; /* Convert to byte address if needed */

	res = RES_ERROR;
	if (send_cmd(CMD17, sector) == 0) { /* READ_SINGLE_BLOCK */

		// bc = 40000;	/* Time counter */
		do { /* Wait for response */
			rc = rcv_spi();
		} while (rc == 0xFF);

		if (rc == 0xFE) { /* A data packet arrived */

			bc = 512 + 2 - offset - count; /* Number of trailing bytes to skip */

			/* Skip leading bytes */
			while (offset--)
				rcv_spi();

			/* Receive a part of the sector */
			if (buff) { /* Store data to the memory */
				do {
					*buff++ = rcv_spi();
				} while (--count);
			} else { /* Forward data to the outgoing stream */
				do {
					// FORWARD(rcv_spi());
				} while (--count);
			}

			/* Skip trailing bytes and CRC */
			do
				rcv_spi();
			while (--bc);

			res = RES_OK;
		}
	}

	DESELECT();
	rcv_spi();

	return res;
}

	/*-----------------------------------------------------------------------*/
	/* Write partial sector                                                  */
	/*-----------------------------------------------------------------------*/

#if _USE_WRITE
DRESULT disk_writep(const BYTE *buff, /* Pointer to the bytes to be written (NULL:Initiate/Finalize sector write) */
                    DWORD       sc    /* Number of bytes to send, Sector number (LBA) or zero */
)
{
	DRESULT     res;
	UINT        bc;
	static UINT wc; /* Sector write counter */

	res = RES_ERROR;

	if (buff) { /* Send data bytes */
		bc = sc;
		while (bc && wc) { /* Send data bytes to the card */
			xmit_spi(*buff++);
			wc--;
			bc--;
		}
		res = RES_OK;
	} else {
		if (sc) { /* Initiate sector write process */
			if (!(CardType & CT_BLOCK))
				sc *= 512;                  /* Convert to byte address if needed */
			if (send_cmd(CMD24, sc) == 0) { /* WRITE_SINGLE_BLOCK */
				xmit_spi(0xFF);
				xmit_spi(0xFE); /* Data block header */
				wc  = 512;      /* Set byte counter */
				res = RES_OK;
			}
		} else { /* Finalize sector write process */
			bc = wc + 2;
			while (bc--) {
				xmit_spi(0); /* Fill left bytes and CRC with zeros */
			}
			do {
				res = rcv_spi();
			} while (res == 0xFF);
			if ((res & 0x1F) == 0x05) { /* Receive data resp and wait for end of write process in timeout of 500ms */
				for (bc = 5000; rcv_spi() != 0xFF && bc; bc--) /* Wait for ready */
					_delay_us(100);
				if (bc)
					res = RES_OK;
			}
			DESELECT();
			rcv_spi();
		}
	}

	return res;
}
#endif

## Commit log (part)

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2023-03-18 Initial schematics
2023-03-21 Initial software for AVR
2023-03-22 Explained about Fuse bit setting for external clock.
2023-03-22 Update clock settings.
2023-03-23 Editorial update.
2023-03-23 ioport test
2023-03-23 Add document for /INT4.
2023-03-25 Set PORTF as input.
2023-03-26 Patch ioport.h to support ATmega128.
    The calculation of the GPIO register address(PORTA-PORTE) was incorrect because the incorrect definition of IOPORT_PORTx definition for ATmega128.
2023-03-29 Removed IOPORT service of ASF
2023-03-30 Update Design.md
    Fixed misdescription about PG4 and PG5 of AVR.
    Added XMEM interface description.
2023-04-01 UART I/O and XMODEM have been tested.
2023-04-01 Add Skelton code of monitor program.
2023-04-02 Update monitor
    support hex dump.
    xmodem is separated to files.
2023-04-02 Support x_get_s() instead of x_gets() for safety.
2023-04-03 Refactoring monitor and xmodem.
2023-04-03 Add picture of prototype board layout
2023-04-06 Added heap command.
2023-04-06 prototyping for XMEM interface.
2023-04-07 Support External SRAM memory dump.
2023-04-09 Update schematics for Z80 /HALT and /NMI.
2023-04-11 Debug XMEM interface and external SRAM.
2023-04-17 Bug fix: unexpected command execution in Tiny Monitor.
2023-04-17 Bugfix: r and w command of Tiny Monitor.
2023-04-29 74HC574 and 245 are changed to 74HCT.
2023-04-30 Added wave form of read/write between AVR and SRAM.
2023-04-30 Verified XMEM interface.
    Bugfix and update tiny monitor.
    Make Z80 halt at reset.
2023-04-30 Refactoring tiny monitor and XMEM access.
2023-05-01 Changed USB power line connection.
2023-05-02 Update Reset circuit and Serial interface
2023-05-03 Removed ASF delay routines.
    Added isr.[ch].
    Moved PortD settings just after boot.
2023-05-04 Added memory read(M1) and write timing picture.
2023-06-03 Update initial sequence and added debug LED handling.
2023-06-04 Update RESET circuit using DS1232N.
2023-06-06 Added periodic interrupt by Timer0
2023-06-08 Update ISR.
2023-06-09 Fixed bug of WAIT generator circuit
    Clock circuit is moved to 2nd layer.
2023-06-11 Refactoring
2023-06-15 Update diary
2023-06-17 Update ISR to handle INT0,1 and 4
2023-06-17 Add the analysis of the problem in Z80 IN instruction.
2023-06-18 Support downloading Z80 program of INTEL HEX into external memory
2023-06-19 Setup Z80 cross-assemble environment using Dev Container
2023-06-20 Update z80 toolchain configuration
2023-06-20 Add lacks of state transition of Intel hex parser.
2023-06-20 Modified unzip options and sanitize Makefile
2023-06-20 Added echo back code to int handler
2023-06-23 Fixed document regarding Z80 INT support.
2023-06-24 Bug fix of vector table.
2023-06-25 Bug fix of the check sum calculation of INTEL HEX converter.
2023-06-25 Added bload command.
2023-06-25 RX1 echo back test with Z80.
2023-06-25 Update development log.
2023-06-25 Bug fix of echo back program of Z80.
2023-06-26 Support buffered I/O for UART1
2023-06-27 Update development log
2023-07-01 Support emulated device
2023-07-01 Added emulated device specification
2023-07-02 Support Timer2 interrupt every 10ms.
2023-07-02 Update development log and Design document regarding Z80 Mode2 interrupt.
2023-07-04 Bugfix of /BUSACK check
2023-07-04 Bug fix of /BUSACK handling during Z80 /RESET is low at power on/manual reset.
2023-07-08 Update console I/O of EmulatedDeviceSpec.
2023-07-08 Initial trial of porting CP/M2.2
2023-07-08 Add LED device and update DISK I/O interrupt of EmulatedDeviceSpec
2023-07-11 Update CP/M bios
2023-07-12 Implemented CP/M BIOS disk read and write but not debug yet.
2023-07-18 Update BIOS and bugfix of /WAIT clear in ISR.
2023-07-19 Changed boot entry point from CBOOT to WBOOT.
2023-07-20 Bugfix of BIOS jump table and initialize INT in WBOOT.
2023-07-22 Update bios
2023-07-23 Debug diskio
2023-07-25 Update sts command.
2023-07-30 Support cpmtools and hexdumpon dev container
2023-08-05 Add DiskParameters.md.
2023-08-08 support continue without deleting breakpoint.
2023-08-09 Changed BIOS CONIN as blocking API.
2023-08-09 Update diary and progress.
2023-08-11 update .gitignore.
2023-08-11 Add DEBUG_PRINT
2023-08-12 Show Z80 registers when break.
2023-08-13 Show stack area when debugger is invoked.
2023-08-13 Fixed the comment about the pull up register of ISP RST.
2023-08-13 Changed port definition of DISK IO.
2023-08-14 Reset sequencer before setting DISK IO parameters.
2023-08-15 Changed Z80 interrupt handling using HALT, and ZORK I got worked!!!
2023-08-20 Update schematics to support LED and DIP SW.
2023-08-20 Support DIP SW
2023-08-20 Trial of new CONOUT scheme (still buggy).
2023-08-27 Pull up ISP CLK by 10K ohm resistor.
2023-08-28 Fixed typo and etc.
2023-09-10 Update CONOUT mechanism.
2023-09-15 Swap R4 and R5, Change min_resolved_spokes 2 to 1.
2023-09-18 Update for PCB design
2023-09-22 Update document and BOM of schematics.
2023-09-27 PCB Rev1.00
2023-09-30 Workaround for infinite loading of CPP+BDOS.
2023-10-01 Bugfix of disk write.
2023-10-01 Change the default drive in case of an error in SELDSK..
2023-10-01 Update schematics and document.
2023-10-02 Bugfix of WBOOT. Init SP before reloading system.
2023-10-02 Refactoring of disk I/O.
2023-10-04 bugfix of incorrect length in disk write.
2023-10-05 Removed MAX_DISK_NUM because it is no longer necessary.
2023-10-05 Optimized pf_open() and debug macro.
2023-10-05 Update documents.
2023-10-07 Removed z88k from Dockerfile.
2023-10-07 Make standard CP/M image file based on cpm22-b.zip.
2023-10-07 Support CP/M launch from BIOS in AVR EEPROM.
2023-10-08 Refactoring BIOS.
2023-10-08 Launch CP/M when DIPSW4 is ON.
2023-10-08 Refactoring Makefile
2023-10-08 Change DIP SW assignment
    DIPSW1: CP/M launch control
    DIPSW2: UART baud rate
    DIPSW3: N/A
    DIPSW4: SRAM wait
2023-10-09 Refactoring and sanitizing codes.
2023-10-09 Update document structure.
2023-10-10 Removed sdcard.[ch]
2023-10-10 Format source code.
2023-10-11 Update SetupGuide.
2023-10-12 Check if SD Card is inserted in CP/M mode.
2023-10-12 Fixed string bug.
2023-10-12 Update document.
2023-10-12 Update README.
2023-10-12 Add disk image generator.
2023-10-14 Update schematic and pcb.
2023-10-17 Support multiple DPHs of logical disk in BIOS.
2023-10-20 ignore map file
2023-10-21 bugfix of disk write
    In the case that the length of the unaligned sector is less than sizeof(tmpbuf) was not considered.
2023-10-21 small change
2023-10-24 Update PCB, add HW release note
2023-10-26 Update the date of schematics.
2023-10-28 Create fp-lib-table
2023-10-31 Update symbol library setting and property value of schematics diagram.
2023-10-31 Update for MountingHole_Pad.
2023-11-03 Support an empty disk image and ZORK disk image.
2023-11-03 Add usage when using z80/cpm22/sys/CPM.SYS
2023-11-03 Remove zip file so that image does not include it.
2023-11-04 Fixed mkimg.sh problem and update document.
2023-11-05 Update diary.
2023-11-13 Support CP/M 3.
2023-11-16 close #10
2023-12-26 Add FatFs R0.15 w/patch3
2023-12-26 Add mmc_avr sample in ffsample.
2023-12-27 Fixed issue #11
2023-12-28 Support error recovery of disk I/O.
2023-12-28 Update PCB silk
2023-12-28 Update HW-ReleaseNote
2024-01-21 Added local diskdefs for the fix of Issue#13.
2024-04-22 Update comment
2026-03-12 Added Dev Container setup instructions
2026-03-12 Added CP/M disk image troubleshooting
2026-03-12 Update Diary4
2026-03-22 BUG #4: Replace cli()/sei() with SREG save/restore in x_enqueue/x_dequeue/x_flush
    Replace unconditional sei() with SREG save/restore pattern in
    x_enqueue(), x_dequeue(), and x_flush() to preserve the caller's
    interrupt state. When called from ISR context, sei() would
    prematurely re-enable interrupts before the ISR completes,
    widening the race window for BUG #1.
    Severity: MODERATE
2026-03-22 BUG #11: Replace cli()/sei() with SREG save/restore in disk status functions
    Replace unconditional sei() with SREG save/restore pattern in
    IN_0E_DSK_WriteStatus() and IN_13_DSK_ReadStatus(). These functions
    are called from INT0 ISR (Z80 IN instruction handler), which is a
    normal ISR with interrupts disabled. The sei() call prematurely
    re-enables interrupts before the ISR completes, same pattern as BUG #4.
    Severity: MODERATE
2026-03-22 BUG #13: Add volatile to ConsoleBuffer head/tail/count fields
    ConsoleBuffer's head, tail, and count fields are accessed from
    multiple ISR contexts (USART1_RX, INT0, INT1, Timer0). Without
    volatile, the compiler may cache these values in registers,
    causing stale buffer status reports to Z80.
    Severity: MODERATE
    Files: avr/src/xconsoleio.h
2026-03-22 BUG #5: Add z80_int_num_tx1 < 128 guard to Transmit_TX1_Buf()
    Add the same guard check that Enqueue_RX1_Buf() already has, to
    prevent Z80_EXTINT_low() from being called before the interrupt
    number is initialized (z80_int_num_tx1 defaults to 128 until BOOT
    sets it to 2).
    Severity: LOW
    Files: avr/src/emuldev/em_consoleio.c
2026-03-22 BUG #12: Check x_enqueue return value in Enqueue_RX1_Buf and expand RX buffer
    1. Check x_enqueue() return value: when buffer is full (returns 3),
    skip Z80_EXTINT_low() to prevent spurious interrupt notification.
    UDR1 is already consumed at this point so data loss is unavoidable,
    but at least we avoid sending a false CONIN interrupt to Z80.
    2. Increase RX1_BUF_SIZE from 8 to 64 bytes to reduce buffer overflow
    frequency during fast typing or paste operations. SRAM cost: +56 bytes.
2026-03-22 BUG #14: Make Transmit_TX1_Buf() non-blocking
    Replace USART1_Transmit() (busy-wait on UDRE1) with a pre-check of
    UDRE1 flag. If UART TX buffer is busy, skip this Timer0 cycle and
    try again next millisecond. This eliminates ISR-internal busy-wait
    that blocks all interrupts.
    At 9600 bps, approximately 1 in 52 characters will be deferred by
    1ms. At 19200 bps, no change in behavior.
2026-03-22 BUG #6: Add rejection retry to LOAD_CCP_BDOS
    The normal READ path (RETRY_READ) handles rejection status (4) by
    retrying, but LOAD_CCP_BDOS treated all non-zero status as fatal
    error leading to BOOT_ERROR_HALT. This caused system halt during
    warm boot when AVR rejects the read due to an in-progress write.
    Add CP 4 / JR Z retry loop matching the RETRY_READ pattern.
    Severity: CRITICAL
2026-03-22 BUG #8: Add re-entry guard to Timer2 ISR (ISR_NOBLOCK)
    Timer2 ISR uses ISR_NOBLOCK which re-enables interrupts immediately.
    If SD card operations take >10ms, the next Timer2 interrupt causes
    re-entry, accumulating stack frames and risking stack overflow
    (ATmega128 has only 4KB SRAM).
    Add a static volatile bool guard that prevents re-entry of the
    disk I/O and heartbeat sections. disk_timerproc() is kept outside
2026-03-22 BUG #9: Uncomment EI before HALT in DEBUGGER handler
    With EI commented out, Z80 enters HALT in DI (interrupts disabled)
    state, making it impossible to resume via INT from dbg_Continue().
    Only NMI or reset can recover.
    Uncomment EI so that HALT can be released by the INT 4 interrupt
    sent by the AVR debugger.
    Severity: IMPORTANT
2026-03-22 BUG #2: Reorder cli()/ExtMem_attach() in em_diskio.c
    - Move ExtMem_attach() before cli() so bus acquisition happens
    with interrupts enabled (allows INT0/INT1 to be serviced)
    - Limit cli() scope to memcpy only (SREG save/restore pattern)
    - Replace sei() with SREG restore for safer interrupt state handling
    - Applied to all 5 cli/ExtMem_attach blocks:
    - em_disk_write: unaligned head (L339)
2026-03-22 BUG #7: Add debug assertion for SELDSK during active I/O
    Add DEBUG_PRINT_STATE conditional check in OUT_0A_DSK_SelectDisk()
    to detect if SELDSK is called while disk I/O is still in DOING state.
    This is an observation-only change (debug log output) to determine
    if BUG #7 manifests after BUG #1 and BUG #8 fixes are applied.
    When DEBUG_PRINT_STATE is set to 1, a warning message is printed
    if read or write state is DOING at SELDSK entry.
2026-03-23 Add BugFixPlan1.md
